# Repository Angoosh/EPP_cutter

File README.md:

# EPP_cutter
Final exam project <br />
Contains controlling app and gcode sender. <br />
CAM is here: https://bitbucket.org/Zbynek_Dostal/cam-for-hot-wire 

## Installation:
```
git clone https://github.com/Angoosh/EPP_cutter ~/cutter
cd ~/cutter
sudo sh install.sh
```

**Supported distros:** 

&nbsp;&nbsp;&nbsp;&nbsp;&nbsp;&nbsp; Ubuntu 16.04 and up<br />
&nbsp;&nbsp;&nbsp;&nbsp;&nbsp;&nbsp; Raspbian Stretch and up <br />
&nbsp;&nbsp;&nbsp;&nbsp;&nbsp;&nbsp; Arch Linux <br />

Connect your power button to GPIO 3 and GND <br />
Connect your power button light to GPIO 2 and GND <br />
Connect your Emergency button to GPIO 14 and GND <br />
Connect your Emergency button light to GPIO 4 and GND <br />

**IP LED display:**

b7 = GPIO-5     = 128<br />
b6 = GPIO-6     = 64<br />
b5 = GPIO-13    = 32<br />
b4 = GPIO-19    = 16<br />
b3 = GPIO-26    = 8<br />
b2 = GPIO-16    = 4<br />
b1 = GPIO-20    = 2<br />
b0 = GPIO-21    = 1<br />

(all GPIOs are BCM named) <br />
```
sudo usermod -a -G dialout USER_NAME
```
When installation is finished pi will ask for new password. It is password for samba. <br />
Path to samba drive is: <br />
  On Windows: \\\RPI_IP_ADDRESS\ <br />
  On Linux: smb://RPI_IP_ADDRESS/ <br />

When selecting gcode the path is: gcodes/YOUR_GCODE.gcode <br />

Default username is: cutter and password is Pizza <br />

enjoy!

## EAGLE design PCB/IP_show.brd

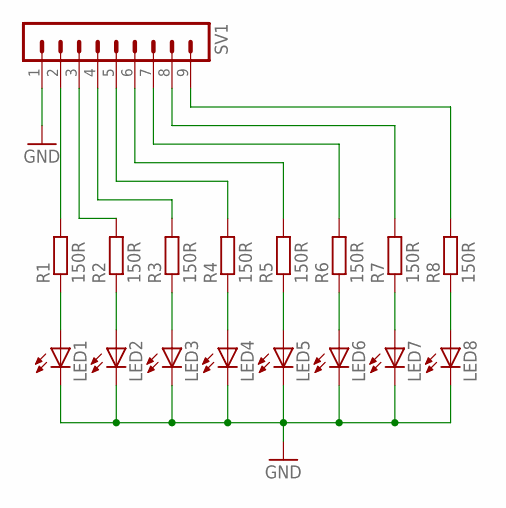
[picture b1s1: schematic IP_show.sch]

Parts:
LED1, LED2, LED3, LED4, LED5, LED6, LED7, LED8: LED_E; LED_1206
R1, R2, R3, R4, R5, R6, R7, R8: 150R; R1206
SV1: MA09-1

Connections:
GND: LED1.C, LED2.C, LED3.C, LED4.C, LED5.C, LED6.C, LED7.C, LED8.C, SV1.1
unnamed: LED8.A, R8.1
unnamed: LED7.A, R7.1
unnamed: LED6.A, R6.1
unnamed: LED5.A, R5.1
unnamed: LED4.A, R4.1
unnamed: LED3.A, R3.1
unnamed: LED2.A, R2.1
unnamed: LED1.A, R1.1
unnamed: R8.2, SV1.9
unnamed: R7.2, SV1.8
unnamed: R6.2, SV1.7
unnamed: R5.2, SV1.6
unnamed: R4.2, SV1.5
unnamed: R3.2, SV1.4
unnamed: R2.2, SV1.3
unnamed: R1.2, SV1.2

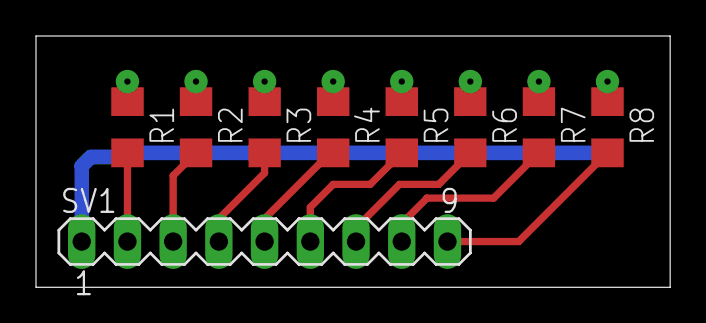
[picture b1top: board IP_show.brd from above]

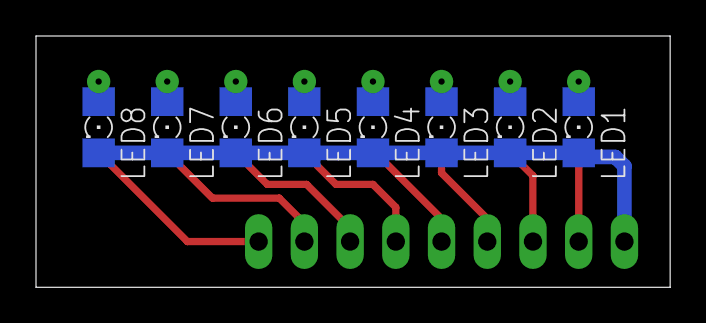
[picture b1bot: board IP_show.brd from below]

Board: 2 copper layers, 35.2 x 14.0 mm, 17 parts (8 on the bottom side), 17 nets.

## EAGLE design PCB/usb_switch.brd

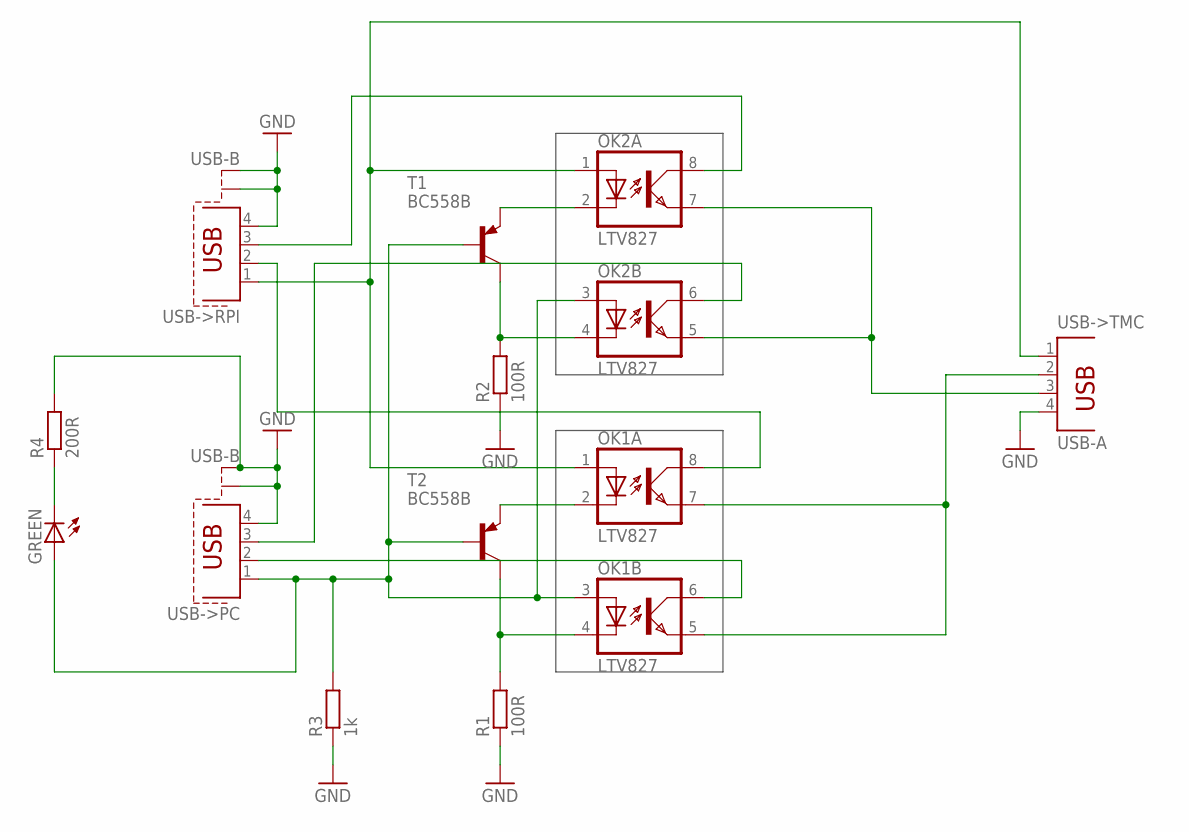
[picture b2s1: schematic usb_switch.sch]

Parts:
GREEN: LED_ELD260; LED_LD260
OK1, OK2: LTV827; DIL08
R1, R2: 100R; 0204/7
R3: 1k; 0204/7
R4: 200R; 0204/7
T1, T2: BC558B; TO92-BEC
USB->PC: USB-B; PN61729-S
USB->RPI: USB-B; PN61729-S
USB->TMC: USB-A; PN87520

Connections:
GND: R1.1, R2.1, R3.1, R4.2, USB->PC.4, USB->PC.S1, USB->PC.S2, USB->RPI.4, USB->RPI.S1, USB->RPI.S2, USB->TMC.4
unnamed: OK2.5 (EMIT), OK2.7 (EMIT), USB->TMC.3
unnamed: OK1.5 (EMIT), OK1.7 (EMIT), USB->TMC.2
unnamed: OK2.4 (C), R2.2, T1.C
unnamed: OK1.4 (C), R1.2, T2.C
unnamed: OK1.2 (C), T2.E
unnamed: OK2.2 (C), T1.E
unnamed: GREEN.A, OK1.3 (A), OK2.3 (A), R3.2, T1.B, T2.B, USB->PC.1
unnamed: OK1.1 (A), OK2.1 (A), USB->RPI.1, USB->TMC.1
unnamed: OK2.8 (COL), USB->RPI.3
unnamed: OK2.6 (COL), USB->PC.3
unnamed: OK1.6 (COL), USB->PC.2
unnamed: OK1.8 (COL), USB->RPI.2
unnamed: GREEN.K (C), R4.1

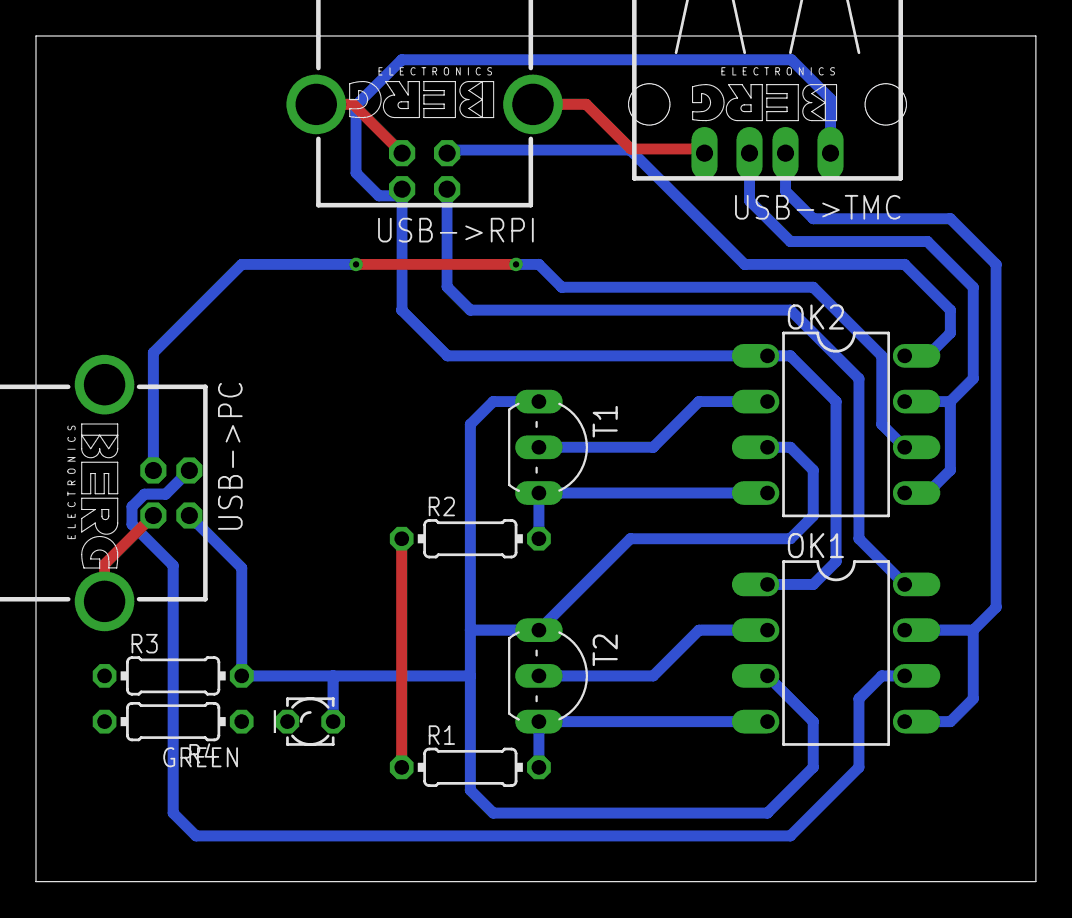
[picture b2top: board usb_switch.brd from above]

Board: 2 copper layers, 55.5 x 47.0 mm, 12 parts (0 on the bottom side), 14 nets.

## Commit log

2018-09-20 Create null
2018-10-29 tmp
    temp file for making of this directory
2018-10-29 Create tmp
    temp file for making of this directory
2018-10-29 added images for buttons and app
2018-10-29 added install.sh
2018-10-30 Added temperature control
2018-10-30 added clear terminal function
    terminal clear function and heater button works too
2018-10-30 terminal clr
    terminal clear function and working heater button
2018-10-30 terminal clr
2018-10-31 freezing issue fix
    moving of motors without freezing GUI works now
2018-10-31 added gcode file filter
2018-11-01 enhanced communications
2018-11-01 added sender.py
2018-11-01 added config file for cutter
2018-11-01 added indicators of set axis position
2018-11-04 sender, gui, config
    sender - great sender update
    gui - minor update for sender compatibility
    config - update for using other microstepping than 255
2018-11-04 added CLI
2018-11-13 update of CLI, GUI and sender
2018-11-13 Responsive GUI
2018-11-13 added fullscreen support via button
2018-11-15 GUI has sorta responsive font size
    Enhanced compatibility with screens smaller than 1280x720
2018-11-28 added automated startup
2018-11-28 added automation script
2018-11-28 general upload
2018-12-01 bash support
2018-12-01 added shell support
2018-12-01 bug fix
2019-01-05 interpolation addedd to G1
2019-01-08 axis naming update
2019-01-08 update of axis naming
2019-01-09 experimenal sender
    In dev sender which uses buffer for smoother operation when cutting precisely
2019-02-04 fix G28
2019-02-04 heater cools down when unknown commad specified
2019-02-05 added login
2019-02-07 added reset of TMC
2019-02-07 position recording
2019-02-09 added M600 Sxx for wait
2019-02-09 added Fxxx for feedrate
2019-03-05 added comments (cs)
2019-03-07 fix + pcb
2019-03-14 Added light sender (experimental feature)
2019-03-18 Sender logging
    Added logging to sender, for teestinf purposes, not tessted yet
2019-03-22 bugfix
2019-04-26 Update?
    Added timecode to log.txt
    mabie bugfix
2019-04-26 Update2?
2019-04-26 bfix
2019-05-06 Added list ports option
2019-05-07 More logs support
2019-05-07 Added log remove time, bugfix
2019-05-09 added dev sender
2019-05-16 Create LICENSE
2019-05-20 multiinstall added, bugfix
